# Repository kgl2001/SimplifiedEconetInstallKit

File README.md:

# Acorn BBC Micro Simplified Econet Installation module
This module significantly reduces the amount of Econet components that need to be soldered directly onto the Beeb motherboard.

Some general notes:

* For use with Issue 4 & Issue 7 model Bs only.
* The source files are to be used with KiCAD v9.0.0 or later.
* The gerber files have been optimised for fabrication by JLCPCB. In particular, there is a 8mmx8mm silkscreen box on the rear of the PCB. This is to allow a 2D barcode, with unique serial number to be printed on the PCB.
* If you want the barcode to be added, then make sure to select this option in the 'Mark on PCB' field, and make sure to select 'Specify position' in the '2D Barcode Position' field, otherwise you will end up with a white 8mm x 8mm box printed on your PCB and a 8mm x 8mm barcode printed at a position of JLCPCBs choosing. Thrust me on this!
* If you don't want the barcode added, then remove the 8mm x 8mm box from the silkscreen layer and regenerate the gerbers. Otherwise you will end up with a white 8mm x 8mm box printed on your PCB.
* A combined CPL / BOM file is included in the gerber directory. Again, this is for use with JLCPCB, if you want to use their PCBA (PCB Assembly) to solder on all the SMD parts.
* You will need to source a suitable 68B54 ADLC IC and solder this onto the PCB in IC10 position.
* You will also need to source suitable round pin headers, and solder these into positions J1..J5 on the underside of the PCB. These headers will then plug into IC sockets on the beeb motherboard.
* Some additional parts will need to be soldered onto the beeb motherboard. These are detailed int he attached SimplifiedInstallationKit_InstallationInstructions_Rev01.pdf document.
* If you want to use the board as a plain ADF-10 style Econet module, install pin headers into J6 & J7 in place of the headers in J1..J5.

Please refer to the following discussion on Stardot for further details: https://stardot.org.uk/forums/viewtopic.php?p=451324#p451324

## Author

The Simplified Econet Installation module is developed and maintained by Ken Lowe.
    
## Hardware License (Creative Commons BY-SA 4.0)

Please see the following link for details: https://creativecommons.org/licenses/by-sa/4.0/

You are free to:

Share - copy and redistribute the material in any medium or format
Adapt - remix, transform, and build upon the material
for any purpose, even commercially.

This license is acceptable for Free Cultural Works.

The licensor cannot revoke these freedoms as long as you follow the license terms.

Under the following terms:

Attribution - You must give appropriate credit, provide a link to the license, and indicate if changes were made. You may do so in any reasonable manner, but not in any way that suggests the licensor endorses you or your use.

ShareAlike - If you remix, transform, or build upon the material, you must distribute your contributions under the same license as the original.

No additional restrictions - You may not apply legal terms or technological measures that legally restrict others from doing anything the license permits.

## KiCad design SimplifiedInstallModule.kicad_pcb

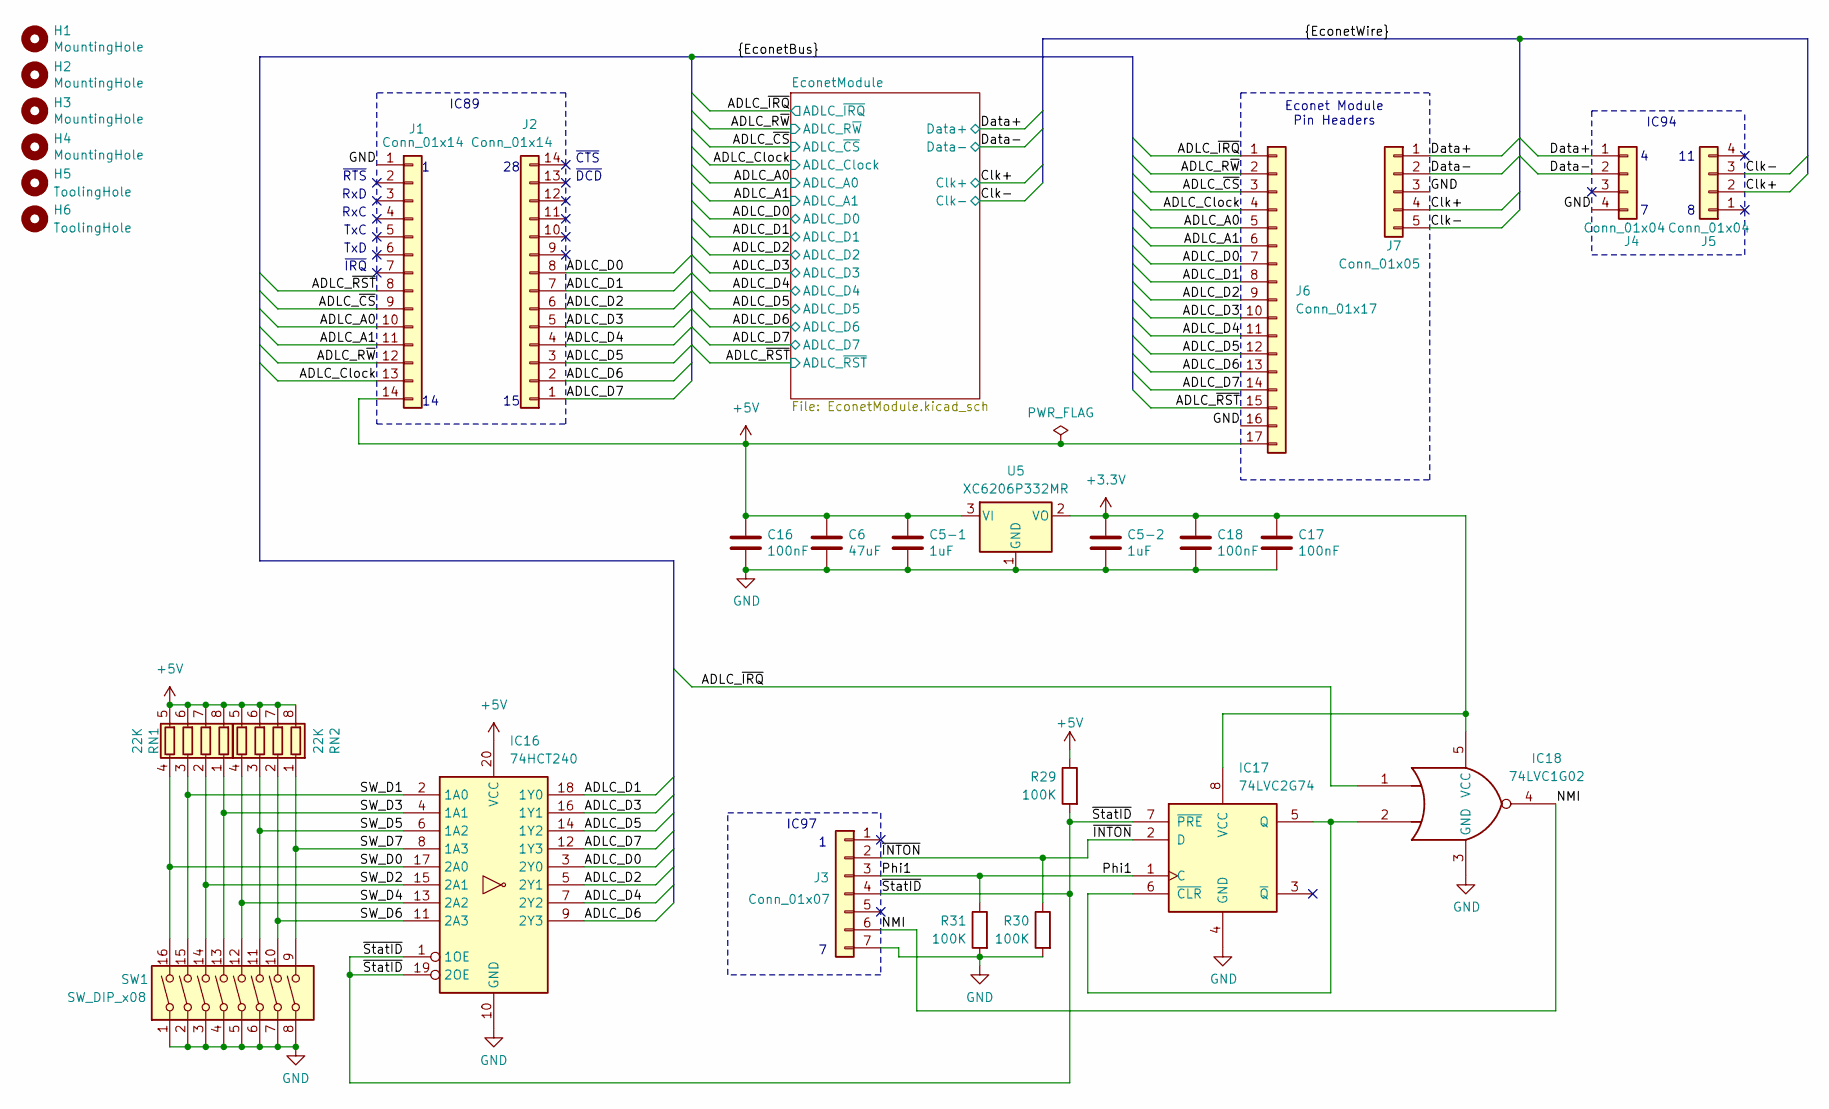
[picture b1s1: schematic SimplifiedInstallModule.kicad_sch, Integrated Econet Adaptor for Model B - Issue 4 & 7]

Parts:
C5-1, C5-2: 1uF; C_0402_1005Metric; JLC Part Number C52923
C6: 47uF; C_0805_2012Metric; JLC Part Number C16780
C16, C17, C18: 100nF; C_0402_1005Metric; Tolerance 10%; JLC Part Number C307331
H1, H2, H3, H4: MountingHole; MountingHole_2.7mm
H5, H6: ToolingHole; ToolingHole 1.152mm
IC16: 74HCT240; SOIC-20W_7.5x12.8mm_P1.27mm; JLC Part Number C132264
IC17: 74LVC2G74; VSSOP-8_2.3x2mm_P0.5mm; JLC Part Number C7851
IC18: 74LVC1G02; SOT-23-5; JLC Part Number C16360
J1, J2: Conn_01x14; PinHeader_1x14_P2.54mm_Vertical
J3: Conn_01x07; PinHeader_1x07_P2.54mm_Vertical
J4, J5: Conn_01x04; PinHeader_1x04_P2.54mm_Vertical
J6: Conn_01x17; PinHeader_1x17_P2.54mm_Vertical
J7: Conn_01x05; PinHeader_1x05_P2.54mm_Vertical
R29, R30, R31: 100K; R_0603_1608Metric; JLC Part Number C25803
RN1, RN2: 22K; R_Array_Concave_4x0603; JLC Part Number C25729
SW1: SW_DIP_x08; SW_DIP_SPSTx08_Slide_Omron_A6S-810x_W8.9mm_P2.54mm; JLC Part Number C311837
U5: XC6206P332MR; SOT-23-3; JLC Part Number C5446

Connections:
+3.3V: C5-2.1, C17.1, C18.1, IC17.8 (VCC), IC18.5 (VCC), U5.2 (VO)
+5V: C5-1.1, C6.1, C16.1, IC16.20 (VCC), J1.14, J6.17, R29.1, RN1.5 (R4.2), RN1.6 (R3.2), RN1.7 (R2.2), RN1.8 (R1.2), RN2.5 (R4.2), RN2.6 (R3.2), RN2.7 (R2.2), RN2.8 (R1.2), U5.3 (VI); also elsewhere on the board
/ADLC_A0: J1.10, J6.5; also elsewhere on the board
/ADLC_A1: J1.11, J6.6; also elsewhere on the board
/ADLC_Clock: J1.13, J6.4; also elsewhere on the board
/ADLC_D0: IC16.3 (2Y0), J2.8, J6.7; also elsewhere on the board
/ADLC_D1: IC16.18 (1Y0), J2.7, J6.8; also elsewhere on the board
/ADLC_D2: IC16.5 (2Y1), J2.6, J6.9; also elsewhere on the board
/ADLC_D3: IC16.16 (1Y1), J2.5, J6.10; also elsewhere on the board
/ADLC_D4: IC16.7 (2Y2), J2.4, J6.11; also elsewhere on the board
/ADLC_D5: IC16.14 (1Y2), J2.3, J6.12; also elsewhere on the board
/ADLC_D6: IC16.9 (2Y3), J2.2, J6.13; also elsewhere on the board
/ADLC_D7: IC16.12 (1Y3), J2.1, J6.14; also elsewhere on the board
/ADLC_R~W: J1.12, J6.2; also elsewhere on the board
/ADLC_~CS: J1.9, J6.3; also elsewhere on the board
/ADLC_~IRQ: IC18.1, J6.1; also elsewhere on the board
/ADLC_~RST: J1.8, J6.15; also elsewhere on the board
/Clk+: J5.2, J7.4; also elsewhere on the board
/Clk-: J5.3, J7.5; also elsewhere on the board
/Data+: J4.1, J7.1; also elsewhere on the board
/Data-: J4.2, J7.2; also elsewhere on the board
/NMI: IC18.4, J3.6
/Phi1: IC17.1 (C), J3.3, R31.1
/SW_D0: IC16.17 (2A0), RN1.4 (R4.1), SW1.16
/SW_D1: IC16.2 (1A0), RN1.3 (R3.1), SW1.15
/SW_D2: IC16.15 (2A1), RN1.2 (R2.1), SW1.14
/SW_D3: IC16.4 (1A1), RN1.1 (R1.1), SW1.13
/SW_D4: IC16.13 (2A2), RN2.4 (R4.1), SW1.12
/SW_D5: IC16.6 (1A2), RN2.3 (R3.1), SW1.11
/SW_D6: IC16.11 (2A3), RN2.2 (R2.1), SW1.10
/SW_D7: IC16.8 (1A3), RN2.1 (R1.1), SW1.9
/~INTON: IC17.2 (D), J3.2, R30.1
/~StatID: IC16.1 (1OE), IC16.19 (2OE), IC17.7 (~PRE), J3.4, R29.2
GND: C5-1.2, C5-2.2, C6.2, C16.2, C17.2, C18.2, IC16.10 (GND), IC17.4 (GND), IC18.3 (GND), J1.1, J3.7, J4.4, J6.16, J7.3, R30.2, R31.2, SW1.1, SW1.2, SW1.3, SW1.4, SW1.5, SW1.6, SW1.7, SW1.8, U5.1 (GND); also elsewhere on the board
unnamed: IC17.5 (Q), IC17.6 (~CLR), IC18.2

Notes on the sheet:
~{CTS}
TxD
IC97
~{IRQ}
~{RTS}
RxD
IC94
RxC
Econet Module Pin Headers
TxC
IC89
~{DCD}

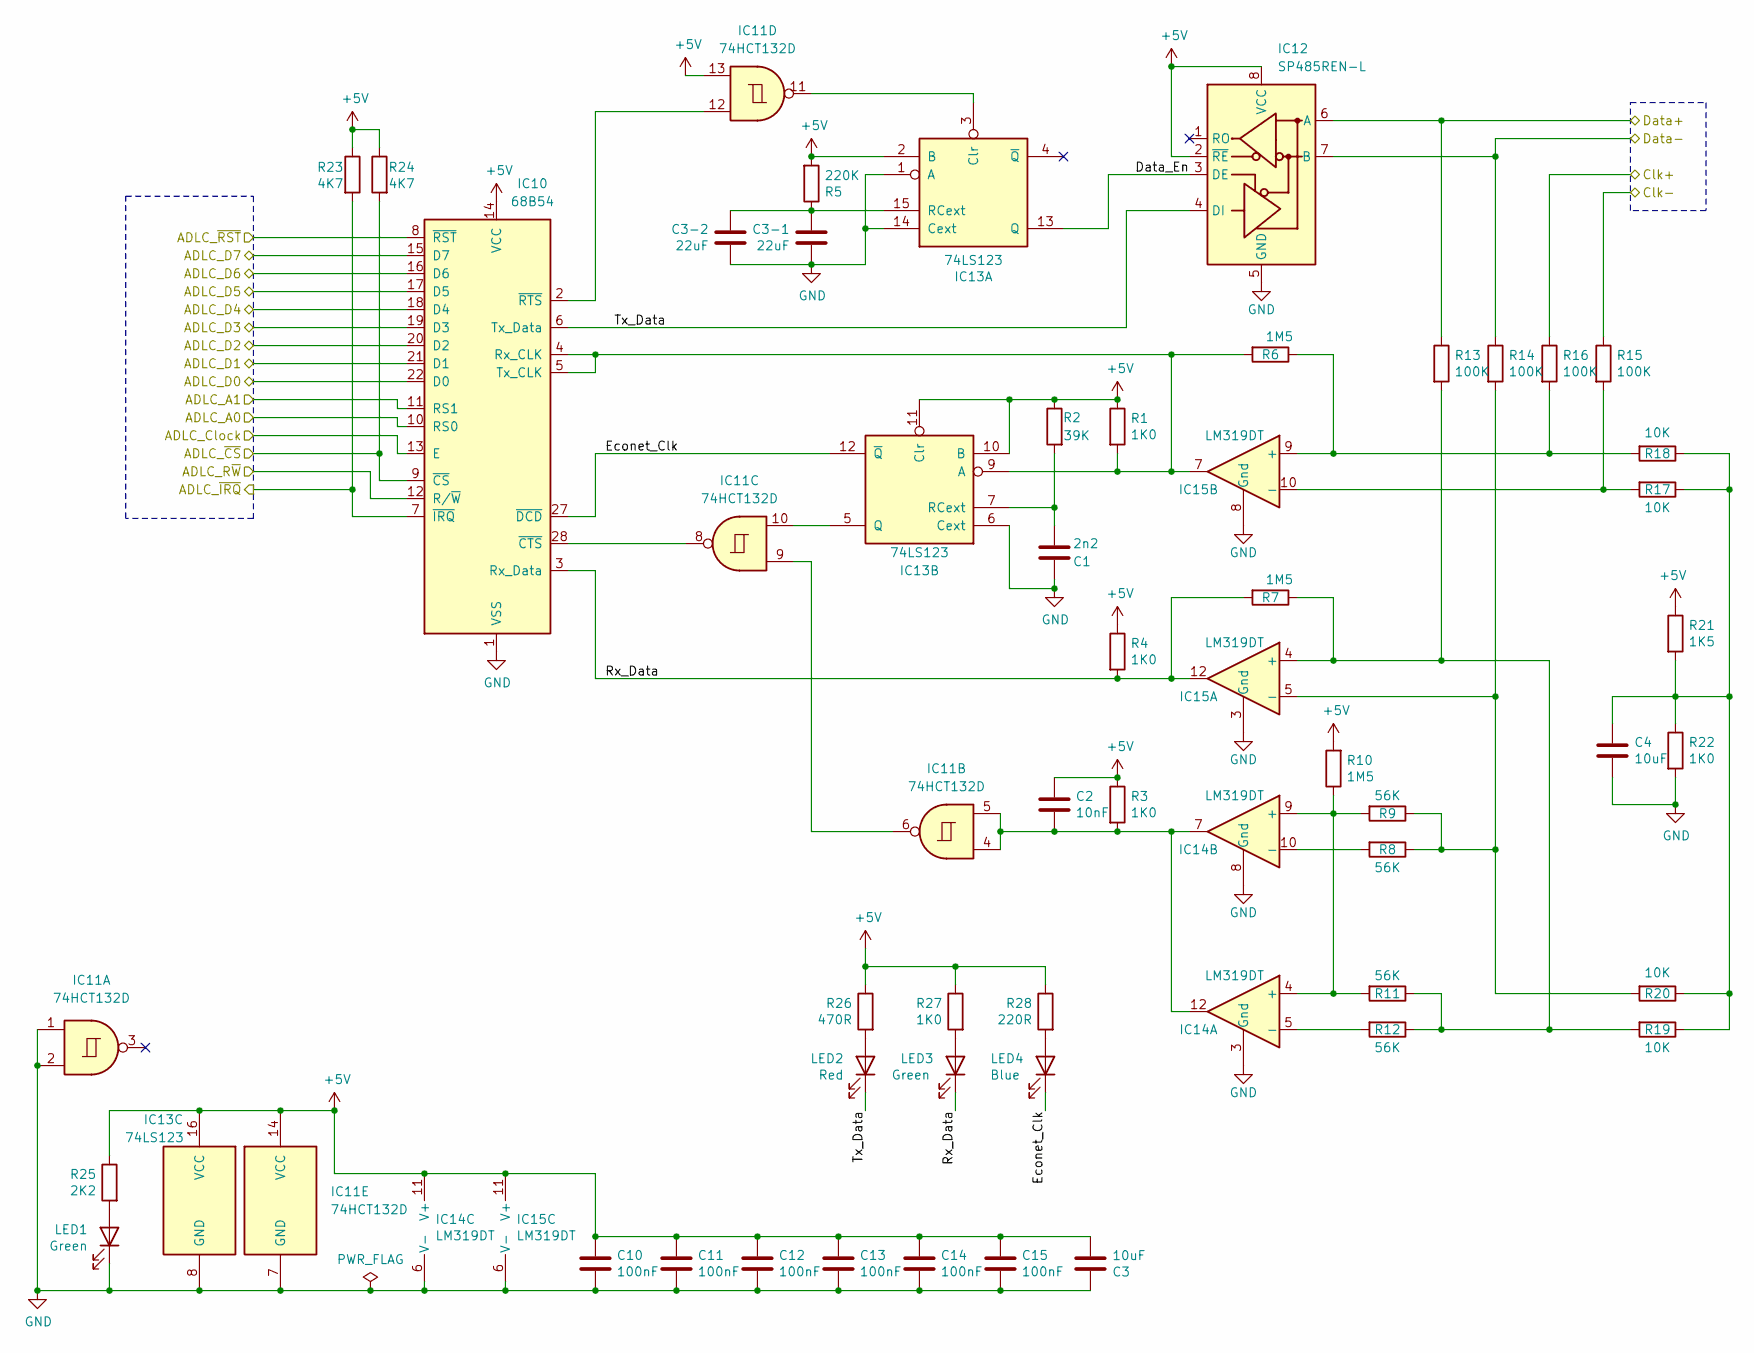
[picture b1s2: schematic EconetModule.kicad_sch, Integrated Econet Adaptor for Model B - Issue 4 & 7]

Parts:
C1: 2n2; C_0805_2012Metric; Tolerance 5%; JLC Part Number C28260
C2: 10nF; C_0603_1608Metric; Tolerance 10%; JLC Part Number C57112
C3, C4: 10uF; C_0603_1608Metric; Tolerance 10%; JLC Part Number C19702
C3-1, C3-2: 22uF; C_0805_2012Metric; Tolerance 20%; JLC Part Number C45783
C10, C11, C12, C13, C14, C15: 100nF; C_0402_1005Metric; Tolerance 10%; JLC Part Number C307331
IC10: 68B54; DIP-28_W15.24mm
IC11: 74HCT132D; SO-14_3.9x8.65mm_P1.27mm; JLC Part Number C5963
IC12: SP485REN-L; SOIC-8_3.9x4.9mm_P1.27mm; JLC Part Number C12545
IC13: 74LS123; SOIC-16_3.9x9.9mm_P1.27mm; JLC Part Number C234231
IC14, IC15: LM319DT; SOIC-14_3.9x8.7mm_P1.27mm; JLC Part Number C143241
LED1, LED3: Green; LED_0603_1608Metric; JLC Part Number C72043
LED2: Red; LED_0603_1608Metric; JLC Part Number C2286
LED4: Blue; LED_0603_1608Metric; JLC Part Number C72041
R1, R3, R4, R22, R27: 1K0; R_0603_1608Metric; Tolerance 1%; JLC Part Number C21190
R2: 39K; R_0603_1608Metric; Tolerance 1%; JLC Part Number C23153
R5: 220K; R_0603_1608Metric; Tolerance 1%; JLC Part Number C22961
R6, R7, R10: 1M5; R_0603_1608Metric; Tolerance 1%; JLC Part Number C4172
R8, R9, R11, R12: 56K; R_0603_1608Metric; Tolerance 1%; JLC Part Number C23206
R13, R14, R15, R16: 100K; R_0603_1608Metric; Tolerance 1%; JLC Part Number C25803
R17, R18, R19, R20: 10K; R_0603_1608Metric; Tolerance 1%; JLC Part Number C25804
R21: 1K5; R_0603_1608Metric; Tolerance 1%; JLC Part Number C22843
R23, R24: 4K7; R_0603_1608Metric; Tolerance 1%; JLC Part Number C23162
R25: 2K2; R_0603_1608Metric; Tolerance 1%; JLC Part Number C4190
R26: 470R; R_0603_1608Metric; Tolerance 1%; JLC Part Number C23179
R28: 220R; R_0603_1608Metric; Tolerance 1%; JLC Part Number C22962

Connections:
+5V: C2.1, C3.2, C10.1, C11.1, C12.1, C13.1, C14.1, C15.1, IC10.14 (VCC), IC11.13, IC11.14 (VCC), IC12.2 (~RE), IC12.8 (VCC), IC13.2 (B), IC13.10 (B), IC13.11 (Clr), IC13.16 (VCC), IC14.11 (V+), IC15.11 (V+), R1.1, R2.1, R3.1, R4.1, R5.2, R10.2, R21.1, R23.1, R24.1, R25.1, R26.1, R27.1, R28.1; also elsewhere on the board
/ADLC_A0: IC10.10 (RS0); also elsewhere on the board
/ADLC_A1: IC10.11 (RS1); also elsewhere on the board
/ADLC_Clock: IC10.13 (E); also elsewhere on the board
/ADLC_D0: IC10.22 (D0); also elsewhere on the board
/ADLC_D1: IC10.21 (D1); also elsewhere on the board
/ADLC_D2: IC10.20 (D2); also elsewhere on the board
/ADLC_D3: IC10.19 (D3); also elsewhere on the board
/ADLC_D4: IC10.18 (D4); also elsewhere on the board
/ADLC_D5: IC10.17 (D5); also elsewhere on the board
/ADLC_D6: IC10.16 (D6); also elsewhere on the board
/ADLC_D7: IC10.15 (D7); also elsewhere on the board
/ADLC_R~W: IC10.12 (R/~W); also elsewhere on the board
/ADLC_~CS: IC10.9 (~CS), R24.2; also elsewhere on the board
/ADLC_~IRQ: IC10.7 (~IRQ), R23.2; also elsewhere on the board
/ADLC_~RST: IC10.8 (~RST); also elsewhere on the board
/Clk+: R16.1; also elsewhere on the board
/Clk-: R15.1; also elsewhere on the board
/Data+: IC12.6 (A), R13.1; also elsewhere on the board
/Data-: IC12.7 (B), R14.1; also elsewhere on the board
/EconetModule/Data_En: IC12.3 (DE), IC13.13 (Q)
/EconetModule/Econet_Clk: IC10.27 (~DCD), IC13.12 (~Q), LED4.1 (K)
/EconetModule/Rx_Data: IC10.3 (Rx_Data), IC15.12, LED3.1 (K), R4.2, R7.2
/EconetModule/Tx_Data: IC10.6 (Tx_Data), IC12.4 (DI), LED2.1 (K)
GND: C1.1, C3.1, C3-1.2, C3-2.2, C4.2, C10.2, C11.2, C12.2, C13.2, C14.2, C15.2, IC10.1 (VSS), IC11.1, IC11.2, IC11.7 (GND), IC12.5 (GND), IC13.1 (A), IC13.6 (Cext), IC13.8 (GND), IC13.14 (Cext), IC14.3 (Gnd), IC14.6 (V-), IC14.8 (Gnd), IC15.3 (Gnd), IC15.6 (V-), IC15.8 (Gnd), LED1.1 (K), R22.2; also elsewhere on the board
unnamed: C2.2, IC11.4, IC11.5, IC14.7, IC14.12, R3.2
unnamed: C4.1, R17.1, R18.1, R19.1, R20.1, R21.2, R22.1
unnamed: IC10.4 (Rx_CLK), IC10.5 (Tx_CLK), IC13.9 (A), IC15.7, R1.2, R6.2
unnamed: IC10.28 (~CTS), IC11.8
unnamed: IC10.2 (~RTS), IC11.12
unnamed: IC11.6, IC11.9
unnamed: IC11.11, IC13.3 (Clr)
unnamed: C3-1.1, C3-2.1, IC13.15 (RCext), R5.1
unnamed: IC11.10, IC13.5 (Q)
unnamed: C1.2, IC13.7 (RCext), R2.2
unnamed: IC14.4 (+), IC14.9 (+), R9.2, R10.1, R11.2
unnamed: IC14.5 (-), R12.2
unnamed: IC14.10 (-), R8.2
unnamed: IC15.4 (+), R7.1, R11.1, R12.1, R13.2, R19.2
unnamed: IC15.5 (-), R8.1, R9.1, R14.2, R20.2
unnamed: IC15.9 (+), R6.1, R16.2, R18.2
unnamed: IC15.10 (-), R15.2, R17.2
unnamed: LED1.2 (A), R25.2
unnamed: LED2.2 (A), R26.2
unnamed: LED3.2 (A), R27.2
unnamed: LED4.2 (A), R28.2

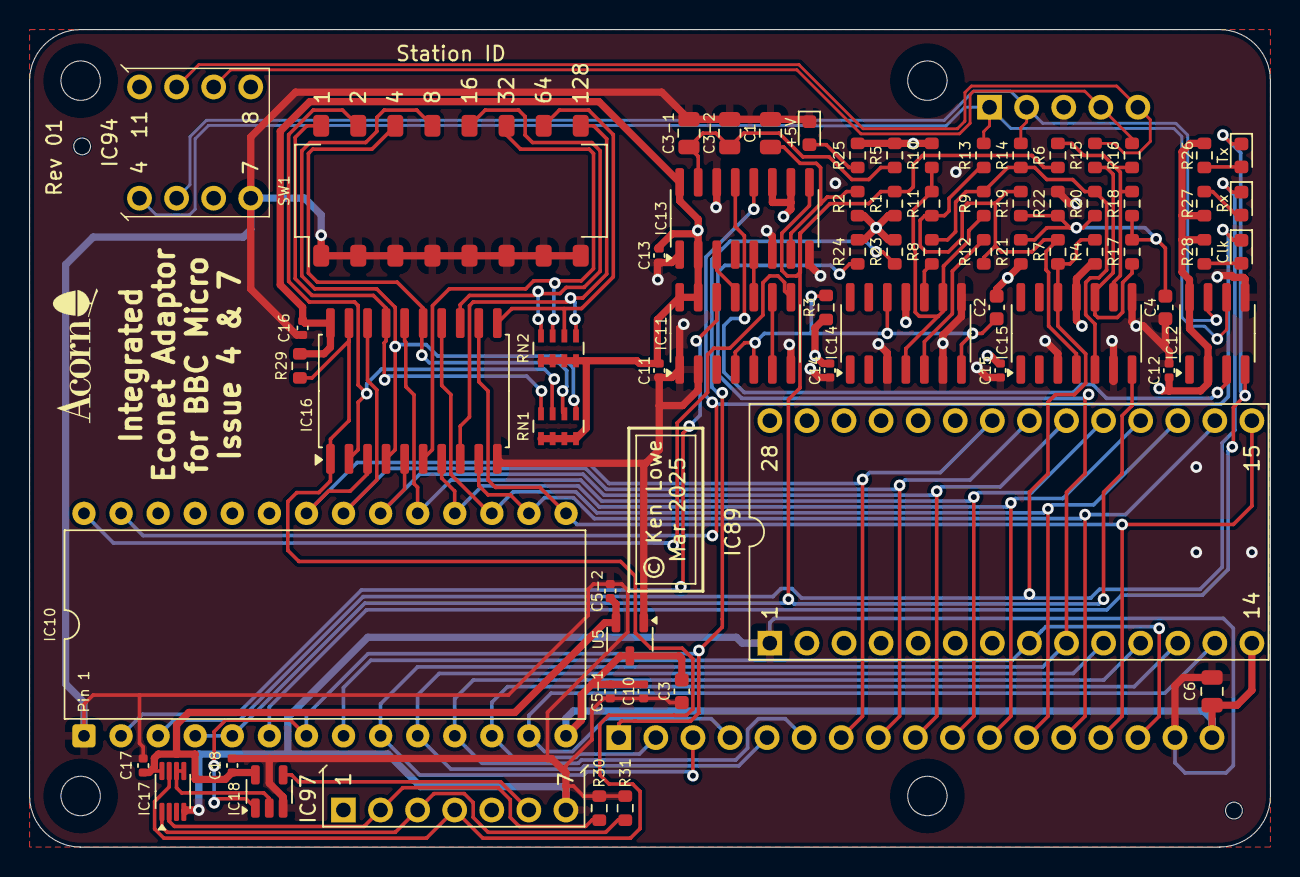
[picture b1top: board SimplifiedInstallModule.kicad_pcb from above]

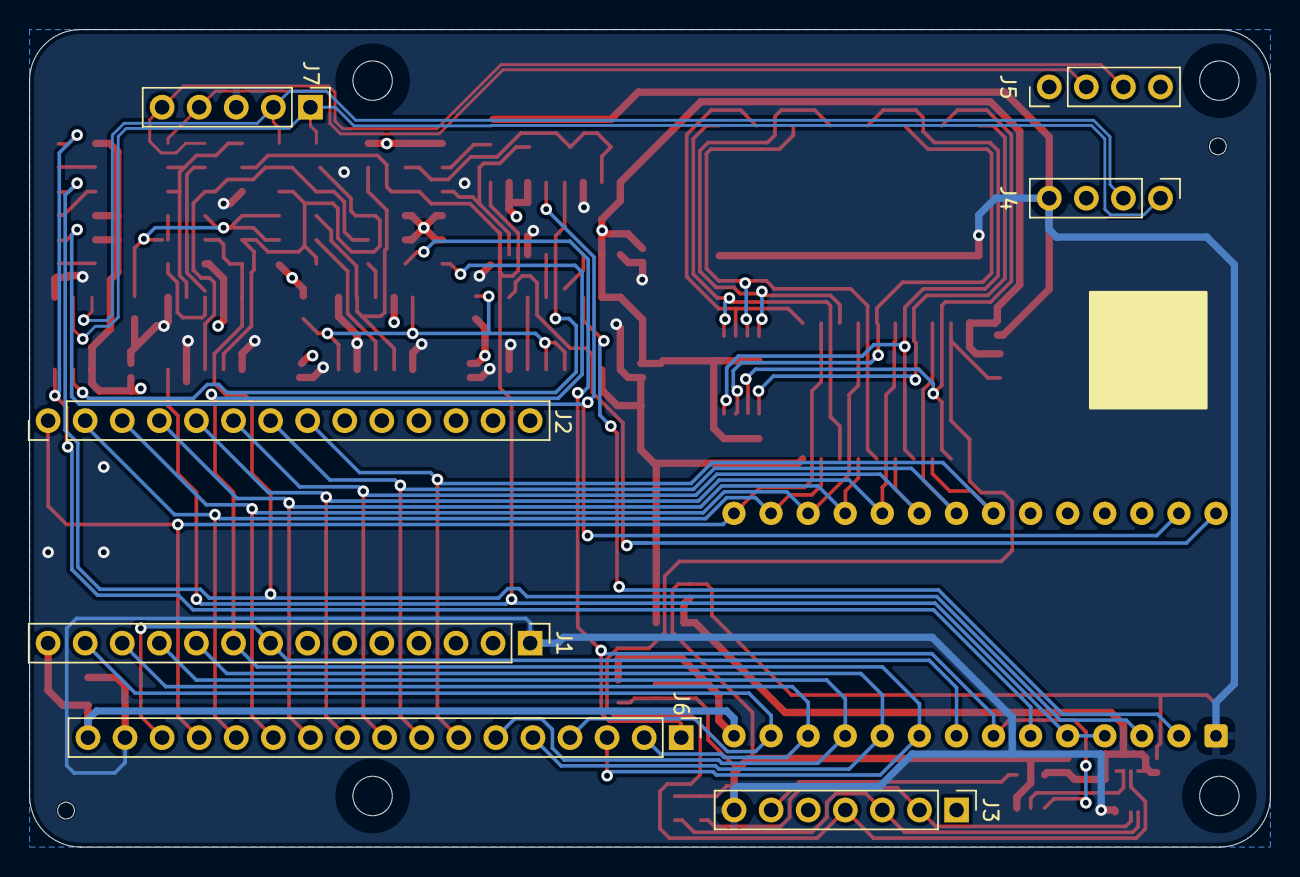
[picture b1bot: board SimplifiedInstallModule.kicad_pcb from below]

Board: 4 copper layers, 85.0 x 56.0 mm, 79 parts (11 on the bottom side), 60 nets.

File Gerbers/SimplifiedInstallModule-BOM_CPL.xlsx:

Designator | JLC Part Number | Footprint | JLCValue | Mid X | Mid Y | Rotation | Layer | Val | Package
C1 | C28260 | 0805 | 2n2 | 148.54485700000001 | -72.657621000000006 | -90 | top | 2n2 | C_0805_2012Metric
C2 | C57112 | 0603 | 10nF | 164.03885700000001 | -84.595620999999994 | -90 | top | 10nF | C_0603_1608Metric
C3 | C19702 | 0603 | 10uF | 142.46885700000001 | -110.884621 | 90 | top | 10uF | C_0603_1608Metric
C3-1 | C45783 | 0805 | 22uF | 142.95685700000001 | -72.657621000000006 | 90 | top | 22uF | C_0805_2012Metric
C3-2 | C45783 | 0805 | 22uF | 145.750857 | -72.657621000000006 | 90 | top | 22uF | C_0805_2012Metric
C4 | C19702 | 0603 | 10uF | 175.595857 | -84.595620999999994 | -90 | top | 10uF | C_0603_1608Metric
C5-1 | C52923 | 0402 | 1uF | 137.56885700000001 | -110.891621 | 90 | top | 1uF | C_0402_1005Metric
C5-2 | C52923 | 0402 | 1uF | 137.56885700000001 | -104.02662100000001 | 90 | top | 1uF | C_0402_1005Metric
C6 | C16780 | 0805 | 47uF | 178.79085699999999 | -110.891621 | 90 | top | 47uF | C_0805_2012Metric
C10 | C307331 | 0402 | 100nF | 139.85485700000001 | -110.891621 | -90 | top | 100nF | C_0402_1005Metric
C11 | C307331 | 0402 | 100nF | 140.924857 | -88.913621000000006 | -90 | top | 100nF | C_0402_1005Metric
C12 | C307331 | 0402 | 100nF | 175.84985699999999 | -88.913621000000006 | 90 | top | 100nF | C_0402_1005Metric
C13 | C307331 | 0402 | 100nF | 140.924857 | -81.039620999999997 | -90 | top | 100nF | C_0402_1005Metric
C14 | C307331 | 0402 | 100nF | 152.608857 | -88.913621000000006 | -90 | top | 100nF | C_0402_1005Metric
C15 | C307331 | 0402 | 100nF | 164.292857 | -88.913621000000006 | -90 | top | 100nF | C_0402_1005Metric
C16 | C307331 | 0402 | 100nF | 116.49685700000001 | -85.999621000000005 | -90 | top | 100nF | C_0402_1005Metric
C17 | C307331 | 0402 | 100nF | 105.57485699999999 | -115.971621 | 90 | top | 100nF | C_0402_1005Metric
C18 | C307331 | 0402 | 100nF | 111.670857 | -115.971621 | 90 | top | 100nF | C_0402_1005Metric
IC11 | C5963 | SOP-14 | 74HCT132D | 146.131857 | -86.373621 | 0 | top | 74HCT132D | SO-14_3.9x8.65mm_P1.27mm
IC12 | C12545 | SOIC-8 | SP485REN-L | 179.15185700000001 | -86.373621 | 0 | top | SP485REN-L | SOIC-8_3.9x4.9mm_P1.27mm
IC13 | C234231 | SOIC-16 | 74LS123 | 146.76685699999999 | -78.499621000000005 | 0 | top | 74LS123 | SOIC-16_3.9x9.9mm_P1.27mm
IC14 | C143241 | SOIC-14 | LM319DT | 157.81585699999999 | -86.373621 | 0 | top | LM319DT | SOIC-14_3.9x8.7mm_P1.27mm
IC15 | C143241 | SOIC-14 | LM319DT | 169.49985699999999 | -86.373621 | 0 | top | LM319DT | SOIC-14_3.9x8.7mm_P1.27mm
IC16 | C132264 | SOIC-20 | 74HCT240 | 124.116857 | -90.317621000000003 | 0 | top | 74HCT240 | SOIC-20W_7.5x12.8mm_P1.27mm
IC17 | C7851 | VSSOP-8 | 74LVC2G74 | 107.60685700000001 | -117.749621 | -90 | top | 74LVC2G74 | VSSOP-8_2.3x2mm_P0.5mm
IC18 | C16360 | SOT-23-5 | 74LVC1G02 | 114.210857 | -117.749621 | -90 | top | 74LVC1G02 | SOT-23-5
LED1 | C72043 | 0603 | Green | 151.21185700000001 | -72.657621000000006 | -90 | top | Green | LED_0603_1608Metric
LED2 | C2286 | 0603 | Red | 180.80285699999999 | -74.181621000000007 | -90 | top | Red | LED_0603_1608Metric
LED3 | C72043 | 0603 | Green | 180.80285699999999 | -77.483620999999999 | -90 | top | Green | LED_0603_1608Metric
LED4 | C72041 | 0603 | Blue | 180.80285699999999 | -80.785621000000006 | -90 | top | Blue | LED_0603_1608Metric
R1 | C21190 | 0603 | 1K0 | 157.05385699999999 | -77.483620999999999 | 90 | top | 1K0 | R_0603_1608Metric
R2 | C23153 | 0603 | 39K | 154.513857 | -77.483620999999999 | 90 | top | 39K | R_0603_1608Metric
R3 | C21190 | 0603 | 1K0 | 152.35485700000001 | -84.595620999999994 | 90 | top | 1K0 | R_0603_1608Metric
R4 | C21190 | 0603 | 1K0 | 170.769857 | -80.785621000000006 | 90 | top | 1K0 | R_0603_1608Metric
R5 | C22961 | 0603 | 220K | 157.05385699999999 | -74.181621000000007 | 90 | top | 220K | R_0603_1608Metric
R6 | C4172 | 0603 | 1M5 | 168.22985700000001 | -74.181621000000007 | -90 | top | 1M5 | R_0603_1608Metric
R7 | C4172 | 0603 | 1M5 | 168.22985700000001 | -80.785621000000006 | -90 | top | 1M5 | R_0603_1608Metric
R8 | C23206 | 0603 | 56K | 159.59385700000001 | -80.785621000000006 | -90 | top | 56K | R_0603_1608Metric
R9 | C23206 | 0603 | 56K | 163.149857 | -77.483620999999999 | -90 | top | 56K | R_0603_1608Metric
R10 | C4172 | 0603 | 1M5 | 159.59385700000001 | -74.181621000000007 | 90 | top | 1M5 | R_0603_1608Metric
R11 | C23206 | 0603 | 56K | 159.59385700000001 | -77.483620999999999 | 90 | top | 56K | R_0603_1608Metric
R12 | C23206 | 0603 | 56K | 163.149857 | -80.785621000000006 | 90 | top | 56K | R_0603_1608Metric
R13 | C25803 | 0603 | 100K | 163.149857 | -74.181621000000007 | -90 | top | 100K | R_0603_1608Metric
R14 | C25803 | 0603 | 100K | 165.68985699999999 | -74.181621000000007 | -90 | top | 100K | R_0603_1608Metric
R15 | C25803 | 0603 | 100K | 170.769857 | -74.181621000000007 | -90 | top | 100K | R_0603_1608Metric
R16 | C25803 | 0603 | 100K | 173.30985699999999 | -74.181621000000007 | -90 | top | 100K | R_0603_1608Metric
R17 | C25804 | 0603 | 10K | 173.30985699999999 | -80.785621000000006 | -90 | top | 10K | R_0603_1608Metric
R18 | C25804 | 0603 | 10K | 173.30985699999999 | -77.483620999999999 | 90 | top | 10K | R_0603_1608Metric
R19 | C25804 | 0603 | 10K | 165.68985699999999 | -77.483620999999999 | 90 | top | 10K | R_0603_1608Metric
R20 | C25804 | 0603 | 10K | 170.769857 | -77.483620999999999 | 90 | top | 10K | R_0603_1608Metric
R21 | C22843 | 0603 | 1K5 | 165.68985699999999 | -80.785621000000006 | 90 | top | 1K5 | R_0603_1608Metric
R22 | C21190 | 0603 | 1K0 | 168.22985700000001 | -77.483620999999999 | 90 | top | 1K0 | R_0603_1608Metric
R23 | C23162 | 0603 | 4K7 | 157.05385699999999 | -80.785621000000006 | -90 | top | 4K7 | R_0603_1608Metric
R24 | C23162 | 0603 | 4K7 | 154.513857 | -80.785621000000006 | -90 | top | 4K7 | R_0603_1608Metric
R25 | C4190 | 0603 | 2K2 | 154.513857 | -74.181621000000007 | -90 | top | 2K2 | R_0603_1608Metric
R26 | C23179 | 0603 | 470R | 178.262857 | -74.181621000000007 | -90 | top | 470R | R_0603_1608Metric
R27 | C21190 | 0603 | 1K0 | 178.262857 | -77.483620999999999 | 90 | top | 1K0 | R_0603_1608Metric
R28 | C22962 | 0603 | 220R | 178.262857 | -80.785621000000006 | -90 | top | 220R | R_0603_1608Metric
R29 | C25803 | 0603 | 100K | 116.30685699999999 | -88.596620999999999 | -90 | top | 100K | R_0603_1608Metric
R30 | C25803 | 0603 | 100K | 136.816857 | -118.89262100000001 | 90 | top | 100K | R_0603_1608Metric
R31 | C25803 | 0603 | 100K | 138.59485699999999 | -118.89262100000001 | 90 | top | 100K | R_0603_1608Metric
RN1 | C25729 | 0603_x4 | 22K | 134.02285699999999 | -92.730620999999999 | 180 | top | 22K | R_Array_Concave_4x0603
RN2 | C25729 | 0603_x4 | 22K | 134.02285699999999 | -87.396620999999996 | 180 | top | 22K | R_Array_Concave_4x0603
SW1 | C311837 | SW_DIP_SPSTx08 | SW_DIP_x08 | 126.656857 | -76.601620999999994 | 180 | top | SW_DIP_x08 | SW_DIP_SPSTx08_Slide_Omron_A6S-810x_W8.9mm_P2.54mm
U5 | C5446 | SOT-23-3L | XC6206P332MR | 138.912857 | -107.328621 | 90 | top | XC6206P332MR | SOT-23-3

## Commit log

2025-03-24 Add License
2025-03-24 Add README.md
2025-03-24 Delete SimplifiedInstallModule.bak
    Redundant file
2025-03-24 Add Installation Instructions

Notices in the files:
SimplifiedInstallModule.kicad_pcb:
© Ken Lowe
